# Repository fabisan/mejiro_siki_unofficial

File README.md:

# 初めに
勝手に作成したメジロ式配列のキーボードです
完成度は低いです

## 各フォルダの中身
CircuitBoard 
  回路図とガーバーデータ、KiCADデータ 
  JLCPCB
  PCB仕様は
    異なるデザイン：2
    納品形式：面付け済み
  HASL無鉛:$18.80 (5枚)

Firmware
  ファームウェアファイル

KeyCaps
  1uと2uのキーのSTLファイル、1個のみ・複数個バージョン
  JLC3DP
  複数個バージョン
    1u: $0.63
    2U: $1.47

plates
  アクリルプレートの加工図面
  遊舎工房に依頼したらすんなりデザインチェックOKでした
  作り直すので消しました

## 直したいところ
- 2Uキーの幅はもう少し長いと見た目がきれい
- ステムの穴はわずかに大きい。
    応急処置方法:穴をふさぐようにマステを貼って、スイッチに押し付けて取り付ける。(ChatGPT先生直伝)
- スタビライザーを付けたい。Y,#,*がわずかにぐらつく -> ステムを見直したら個人的に要らない気がした
- nキーは、t,kの逆側中央を少し盛り上げたい。完全に平面だと押しづらい
- Pro Micro版も作りたい -> 結局RP2040になりました

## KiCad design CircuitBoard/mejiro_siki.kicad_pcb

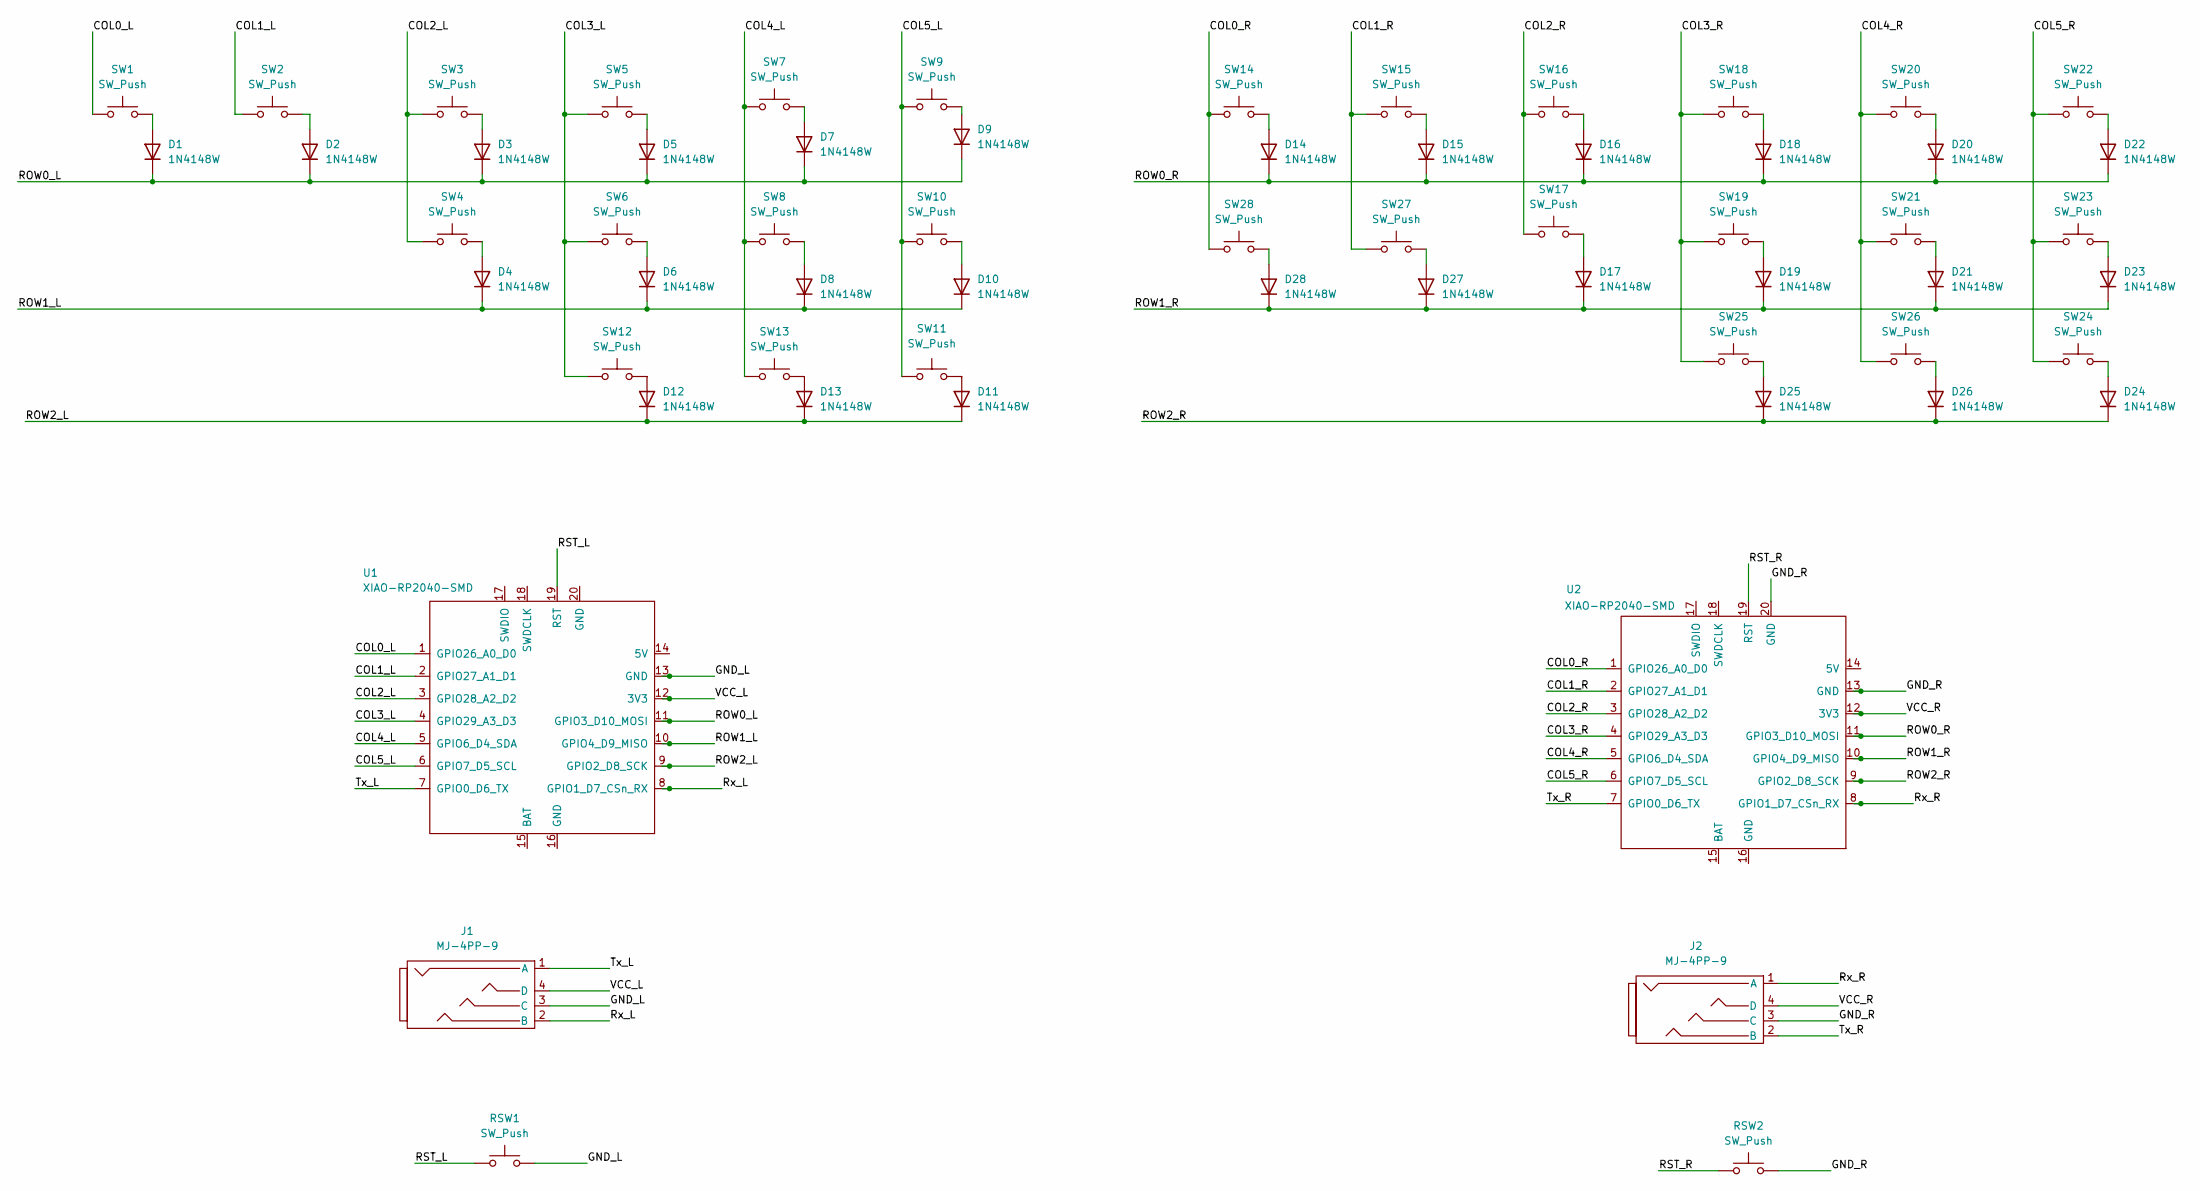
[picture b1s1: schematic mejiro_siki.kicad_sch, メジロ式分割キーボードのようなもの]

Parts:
D1, D2, D3, D4, D5, D6, D7, D8, D9, D10, D11, D12, D13, D14, D15, D16, D17, D18, D19, D20, D21, D22, D23, D24, D25, D26, D27, D28: 1N4148W; D_SOD-123
J1, J2: MJ-4PP-9
RSW1, RSW2: SW_Push; SKHLLCA010
SW1, SW2, SW3, SW4, SW5, SW6, SW7, SW8, SW9, SW10, SW11, SW12, SW13, SW14, SW15, SW16, SW17, SW18, SW19, SW20, SW21, SW22, SW23, SW24, SW25, SW26, SW27, SW28: SW_Push; CherryMX_Hotswap_via_1U
U1, U2: XIAO-RP2040-SMD

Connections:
/COL0_L: SW1.1, U1.1 (GPIO26_A0_D0)
/COL0_R: SW14.1, SW28.1, U2.1 (GPIO26_A0_D0)
/COL1_L: SW2.1, U1.2 (GPIO27_A1_D1)
/COL1_R: SW15.1, SW27.1, U2.2 (GPIO27_A1_D1)
/COL2_L: SW3.1, SW4.1, U1.3 (GPIO28_A2_D2)
/COL2_R: SW16.1, SW17.1, U2.3 (GPIO28_A2_D2)
/COL3_L: SW5.1, SW6.1, SW12.1, U1.4 (GPIO29_A3_D3)
/COL3_R: SW18.1, SW19.1, SW25.1, U2.4 (GPIO29_A3_D3)
/COL4_L: SW7.1, SW8.1, SW13.1, U1.5 (GPIO6_D4_SDA)
/COL4_R: SW20.1, SW21.1, SW26.1, U2.5 (GPIO6_D4_SDA)
/COL5_L: SW9.1, SW10.1, SW11.1, U1.6 (GPIO7_D5_SCL)
/COL5_R: SW22.1, SW23.1, SW24.1, U2.6 (GPIO7_D5_SCL)
/GND_L: J1.3 (C), RSW1.2, U1.13 (GND)
/GND_R: J2.3 (C), RSW2.2, U2.13 (GND), U2.20 (GND)
/ROW0_L: D1.1 (K), D2.1 (K), D3.1 (K), D5.1 (K), D7.1 (K), D9.1 (K), U1.11 (GPIO3_D10_MOSI)
/ROW0_R: D14.1 (K), D15.1 (K), D16.1 (K), D18.1 (K), D20.1 (K), D22.1 (K), U2.11 (GPIO3_D10_MOSI)
/ROW1_L: D4.1 (K), D6.1 (K), D8.1 (K), D10.1 (K), U1.10 (GPIO4_D9_MISO)
/ROW1_R: D17.1 (K), D19.1 (K), D21.1 (K), D23.1 (K), D27.1 (K), D28.1 (K), U2.10 (GPIO4_D9_MISO)
/ROW2_L: D11.1 (K), D12.1 (K), D13.1 (K), U1.9 (GPIO2_D8_SCK)
/ROW2_R: D24.1 (K), D25.1 (K), D26.1 (K), U2.9 (GPIO2_D8_SCK)
/RST_L: RSW1.1, U1.19 (RST)
/RST_R: RSW2.1, U2.19 (RST)
/Rx_L: J1.2 (B), U1.8 (GPIO1_D7_CSn_RX)
/Rx_R: J2.1 (A), U2.8 (GPIO1_D7_CSn_RX)
/Tx_L: J1.1 (A), U1.7 (GPIO0_D6_TX)
/Tx_R: J2.2 (B), U2.7 (GPIO0_D6_TX)
/VCC_L: J1.4 (D), U1.12 (3V3)
/VCC_R: J2.4 (D), U2.12 (3V3)
unnamed: D1.2 (A), SW1.2
unnamed: D2.2 (A), SW2.2
unnamed: D3.2 (A), SW3.2
unnamed: D4.2 (A), SW4.2
unnamed: D5.2 (A), SW5.2
unnamed: D6.2 (A), SW6.2
unnamed: D7.2 (A), SW7.2
unnamed: D8.2 (A), SW8.2
unnamed: D9.2 (A), SW9.2
unnamed: D10.2 (A), SW10.2
unnamed: D11.2 (A), SW11.2
unnamed: D12.2 (A), SW12.2
unnamed: D13.2 (A), SW13.2
unnamed: D14.2 (A), SW14.2
unnamed: D15.2 (A), SW15.2
unnamed: D16.2 (A), SW16.2
unnamed: D17.2 (A), SW17.2
unnamed: D18.2 (A), SW18.2
unnamed: D19.2 (A), SW19.2
unnamed: D20.2 (A), SW20.2
unnamed: D21.2 (A), SW21.2
unnamed: D22.2 (A), SW22.2
unnamed: D23.2 (A), SW23.2
unnamed: D24.2 (A), SW24.2
unnamed: D25.2 (A), SW25.2
unnamed: D26.2 (A), SW26.2
unnamed: D27.2 (A), SW27.2
unnamed: D28.2 (A), SW28.2

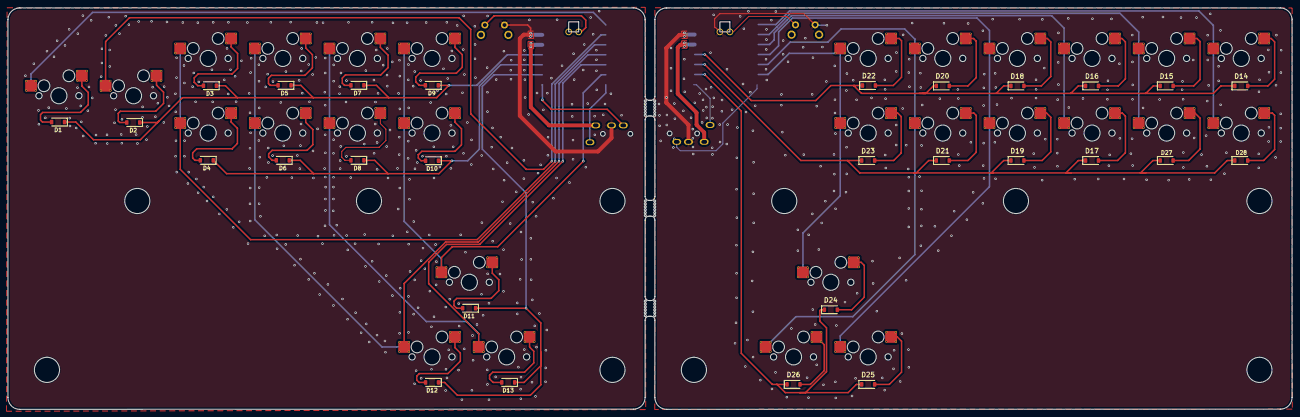
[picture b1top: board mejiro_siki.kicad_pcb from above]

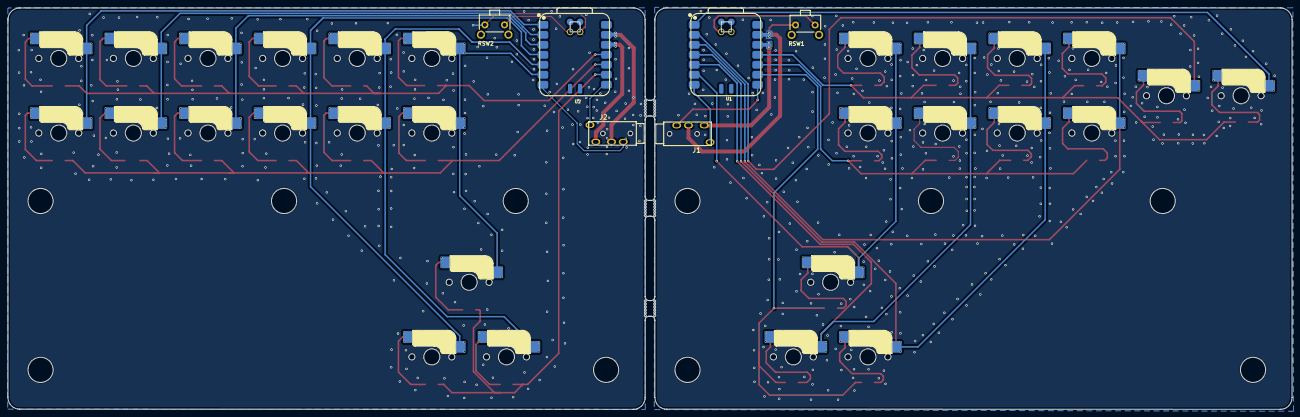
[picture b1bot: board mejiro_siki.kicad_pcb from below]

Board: 2 copper layers, 326.9 x 102.2 mm, 75 parts (6 on the bottom side), 56 nets.

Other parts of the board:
MB1, MB2, MB3: mousebites 2mm; mousebites_2.5mm
SP1, SP2, SP3, SP4, SP5, SP6, SP7, SP8, SP9, SP10: MountingHole_6.4mm_M6

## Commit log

2025-07-06 基板、1uキーキャップほぼ完成
2025-07-06 2uサイズキー完成
2025-07-06 2u 3個セット
2025-07-06 ガーバーファイル追加
2025-07-06 遊舎工房依頼用ファイル作成
2025-07-19 test
2025-07-19 test2
2025-07-19 buildできるかな？
2025-07-19 フォルダ構成変更
2025-07-19 拡張子修正
2025-07-19 ChatGPT先生の教えに従う
2025-07-19 zmkfirmware/unified-zmk-config-template を参考に
2025-07-19 move build.yml to config
2025-07-19 zmk-configフォルダ内に戻しました
2025-07-19 build.yml を作成
2025-07-19 Rename build.yml to build.yaml
2025-07-19 make config/Boards folder
2025-07-20 add firmware
2025-07-20 ファイル名を間違えていたのを修正
2025-07-21 写真載せときます
2025-07-27 Remake 1u key
2025-07-27 Remake 2u key & Create 2u key for Thumbs
2025-07-27 2キーにフィレットをつけました
2025-08-23 練習用Ankiデッキ作成中
2025-08-28 Ankiデッキ更新
2025-08-28 Ankiデッキ@修正
2025-08-31 Ankiカード随時追加中
2025-09-27 基板更新(laptwing対応)
2025-09-27 回路図更新(laptwing対応)
2025-09-27 ガーバーデータ更新(laptwing対応)
2025-10-19 音節学習用Ankiカード作成
2025-10-22 助詞学習用Ankiカード作成
